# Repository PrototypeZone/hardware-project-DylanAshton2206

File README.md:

# CENG 317 First Class Fall 2023 Submission Sheet

| Student name:                        |Dylan Ashton |
|--------------------------------------|--------------|	
|CENG 317 Hardware Project             |  VNCL4040 |
| Section Letter Code:                 |     OCA   |
|CENG 322 Software Project             |Petasos Express|
| Semester enrolled (incl. year):      |  5th sem 4th year|
| Section Letter Code:                 |           |
|Project choice on bb discussion board |  Prox sensor |
| Sensor/effector name:                |   VNCL4040   |
| I2C address:                         |    0x60   |
| A link to where you will buy it from:|       https://www.sparkfun.com/products/15177    |

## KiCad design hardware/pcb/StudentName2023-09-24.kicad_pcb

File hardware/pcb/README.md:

# Troubleshooting Process adapted from BioBytes
1. Visual Inspection:
Inspect the soldered connections, components, and PCB for any visible solder bridges, cold
solder joints, or misplaced components.
Check for any damage to the components, traces, or PCB.
2. Power and Ground:
Ensure that the power and ground connections are correctly established for all components.
Verify that the power supply voltage matches the requirements of the components.
3. Consult Documentation:
Refer to datasheets and technical documentation for components to ensure correct usage and
connections.
4. Component Orientation:
Double-check that all components, including the LED, ADXL345 sensor, and resistors, are
correctly oriented and soldered in the right positions.
5. Soldering Quality:
Reheat any suspicious solder joints to ensure proper bonding and conductivity.
Remove excess solder or solder bridges with a soldering iron and desoldering wick.
6. Continuity Test:
Use a multimeter's continuity mode to verify that there are no open circuits or breaks in the
traces.
Test the continuity of connections between the components and their corresponding pins on the
PCB.
7. Signal Integrity:
Check if the GPIO pins on the Raspberry Pi are correctly connected to the LED and sensor/effector.
Use a multimeter or oscilloscope to verify that the signals are reaching the correct pins.
8. I2C Communication:
Verify the I2C communication between the Raspberry Pi and the sensor/effector.
Check the sender's address and the Raspberry Pi's I2C settings in the software code.
9. Code Inspection: Scrutinize code for errors and logic flaws.
10. LED Behavior:
If the LED is not blinking as expected, review the software code controlling the LED.
Confirm that the GPIO pin settings and blinking pattern are correctly programmed.
11. Sensor Data:
If the LED behaviour is influenced by the ADXL345 sensor's data, ensure that the sensor is
correctly connected and functioning.
Check if the sensor is providing accurate acceleration data to the Raspberry Pi.
12. Component Replacement:
If a component is suspected to be faulty, consider replacing it with a new one and retest the
circuit.
Ensure that the replacement component is of the same type and specifications.
13. Isolation Testing:
Isolate sections of the circuit to identify specific problem areas.
Test individual components or sections of the PCB to pinpoint the source of the issue.
14. Seek External Help:
If the troubleshooting steps prove challenging, seek advice from experienced individuals, online
communities, or forums.
15. Record Changes and Repeat Testing:
Document any changes made during troubleshooting, including component replacements,
adjustments to code, or modifications to connections. After making changes, repeat testing to
verify whether the issue has been resolved.

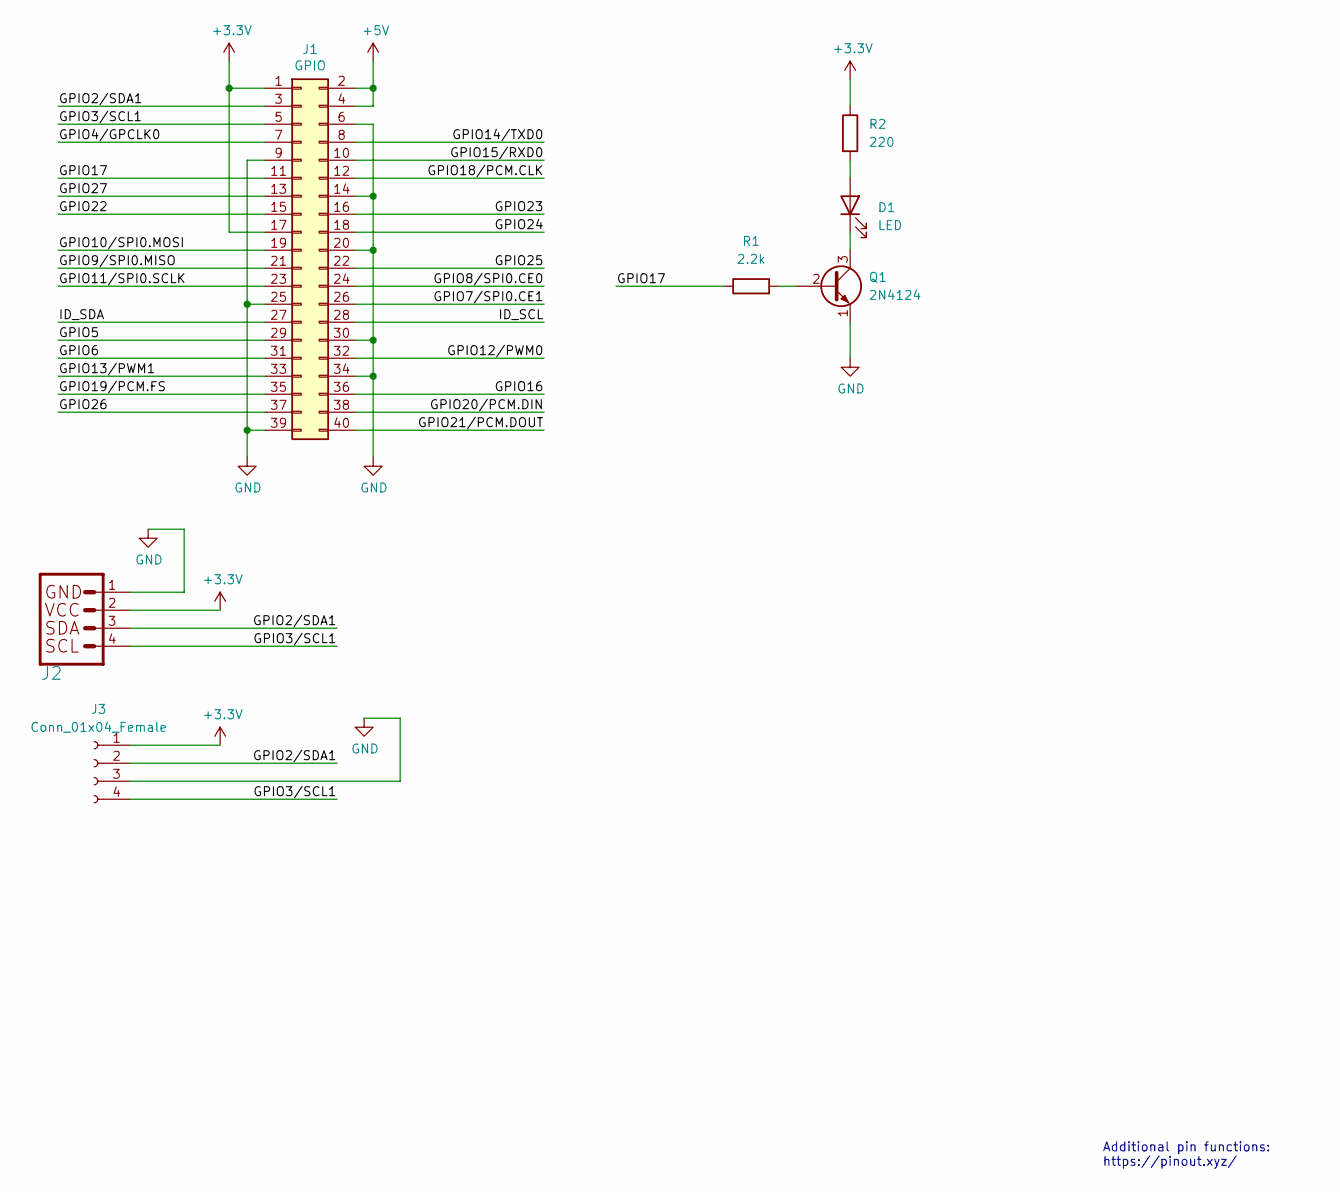
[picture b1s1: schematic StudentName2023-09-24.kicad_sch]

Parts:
D1: LED; LED_D5.0mm_Horizontal_O1.27mm_Z3.0mm
J1: GPIO; PinSocket_2x20_P2.54mm_Vertical
J2: Qwiic Right Angle; JST_SH_SM04B-SRSS-TB_1x04-1MP_P1.00mm_Horizontal
J3: Conn_01x04_Female
Q1: 2N4124; TO-92_HandSolder
R1: 2.2k; R_Axial_DIN0207_L6.3mm_D2.5mm_P10.16mm_Horizontal
R2: 220; R_Axial_DIN0207_L6.3mm_D2.5mm_P10.16mm_Horizontal

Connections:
+3V3: J1.1, J1.17, J2.2, J3.1, R2.1
+5V: J1.2, J1.4
/GPIO2/SDA1: J1.3, J2.3, J3.2
/GPIO3/SCL1: J1.5, J2.4, J3.4
/GPIO4/GPCLK0: J1.7
/GPIO5: J1.29
/GPIO6: J1.31
/GPIO7/SPI0.CE1: J1.26
/GPIO8/SPI0.CE0: J1.24
/GPIO9/SPI0.MISO: J1.21
/GPIO10/SPI0.MOSI: J1.19
/GPIO11/SPI0.SCLK: J1.23
/GPIO12/PWM0: J1.32
/GPIO13/PWM1: J1.33
/GPIO14/TXD0: J1.8
/GPIO15/RXD0: J1.10
/GPIO16: J1.36
/GPIO17: J1.11, R1.1
/GPIO18/PCM.CLK: J1.12
/GPIO19/PCM.FS: J1.35
/GPIO20/PCM.DIN: J1.38
/GPIO21/PCM.DOUT: J1.40
/GPIO22: J1.15
/GPIO23: J1.16
/GPIO24: J1.18
/GPIO25: J1.22
/GPIO26: J1.37
/GPIO27: J1.13
/ID_SCL: J1.28
/ID_SDA: J1.27
GND: J1.6, J1.9, J1.14, J1.20, J1.25, J1.30, J1.34, J1.39, J2.1, J3.3, Q1.1 (E)
unnamed: D1.2 (A), R2.2
unnamed: Q1.2 (B), R1.2
unnamed: D1.1 (K), Q1.3 (C)

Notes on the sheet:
Additional pin functions: https://pinout.xyz/

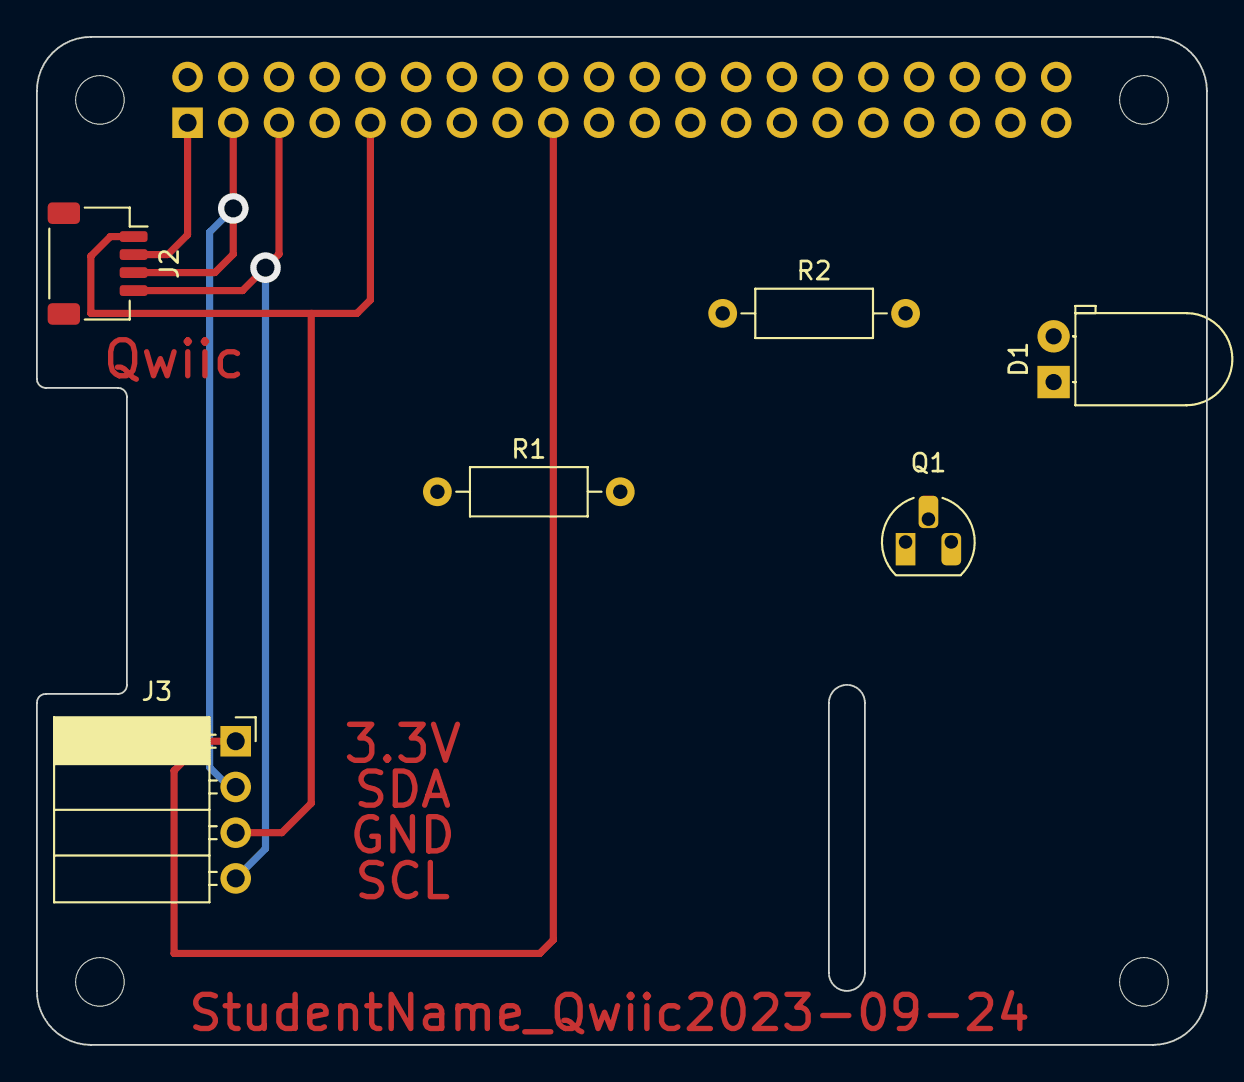
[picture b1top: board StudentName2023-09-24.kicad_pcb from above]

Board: 2 copper layers, 65.0 x 56.0 mm, 11 parts (1 on the bottom side), 9 nets.

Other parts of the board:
MH1, MH2, MH3, MH4: MountingHole_2.7mm_M2.5

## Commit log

2023-09-25 GitHub Classroom Feedback
2023-09-25 Setting up GitHub Classroom Feedback
2023-09-25 Added bom.md
    Bill of materials
2023-09-25 Moved bom.md to hardware and deleted old bom.md
2023-10-16 Added Kicad files --
    F.Cu
    B.Cu
    F.Silkscreen
    B.Silkscreen
    F.Mask
    B.Mask
2023-10-30 added laser cut files and pdf
2023-11-13 added code for prox sensor
2023-11-27 Add files via upload
    fixed powerpoint
2023-11-27 Update VCNL4040.py
    added reading of ambient light
2023-12-05 Update VCNL4040.py
    updates faster
